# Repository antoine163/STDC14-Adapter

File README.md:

# STDC14 Adapter board
STDC14 to SWD and Ftdi 2.54mm header.

## View

## Schematic

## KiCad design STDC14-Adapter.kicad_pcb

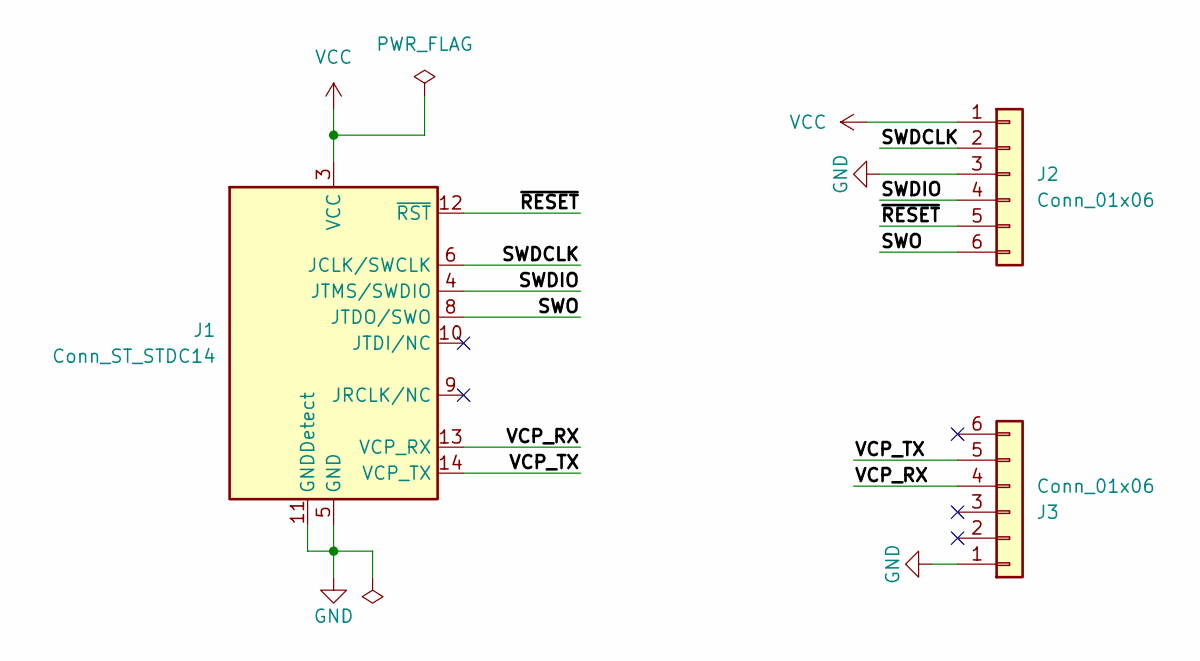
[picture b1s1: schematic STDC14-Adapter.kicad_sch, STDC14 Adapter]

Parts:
J1: Conn_ST_STDC14; PinHeader_2x07_P1.27mm_Vertical_SMD
J2, J3: Conn_01x06; PinHeader_1x06_P2.54mm_Vertical

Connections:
/SWDCLK: J1.6 (JCLK/SWCLK), J2.2
/SWDIO: J1.4 (JTMS/SWDIO), J2.4
/SWO: J1.8 (JTDO/SWO), J2.6
/VCP_RX: J1.13 (VCP_RX), J3.4
/VCP_TX: J1.14 (VCP_TX), J3.5
/~RESET: J1.12 (~RST), J2.5
GND: J1.5 (GND), J1.7 (GND), J1.11 (GNDDetect), J2.3, J3.1
VCC: J1.3 (VCC), J2.1

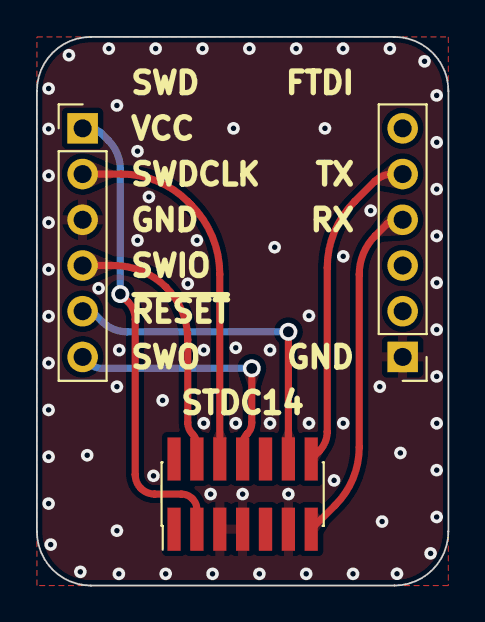
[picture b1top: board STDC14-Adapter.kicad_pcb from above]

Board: 2 copper layers, 22.9 x 30.5 mm, 3 parts (0 on the bottom side), 8 nets.

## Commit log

2024-03-31 update pcb and add production files
